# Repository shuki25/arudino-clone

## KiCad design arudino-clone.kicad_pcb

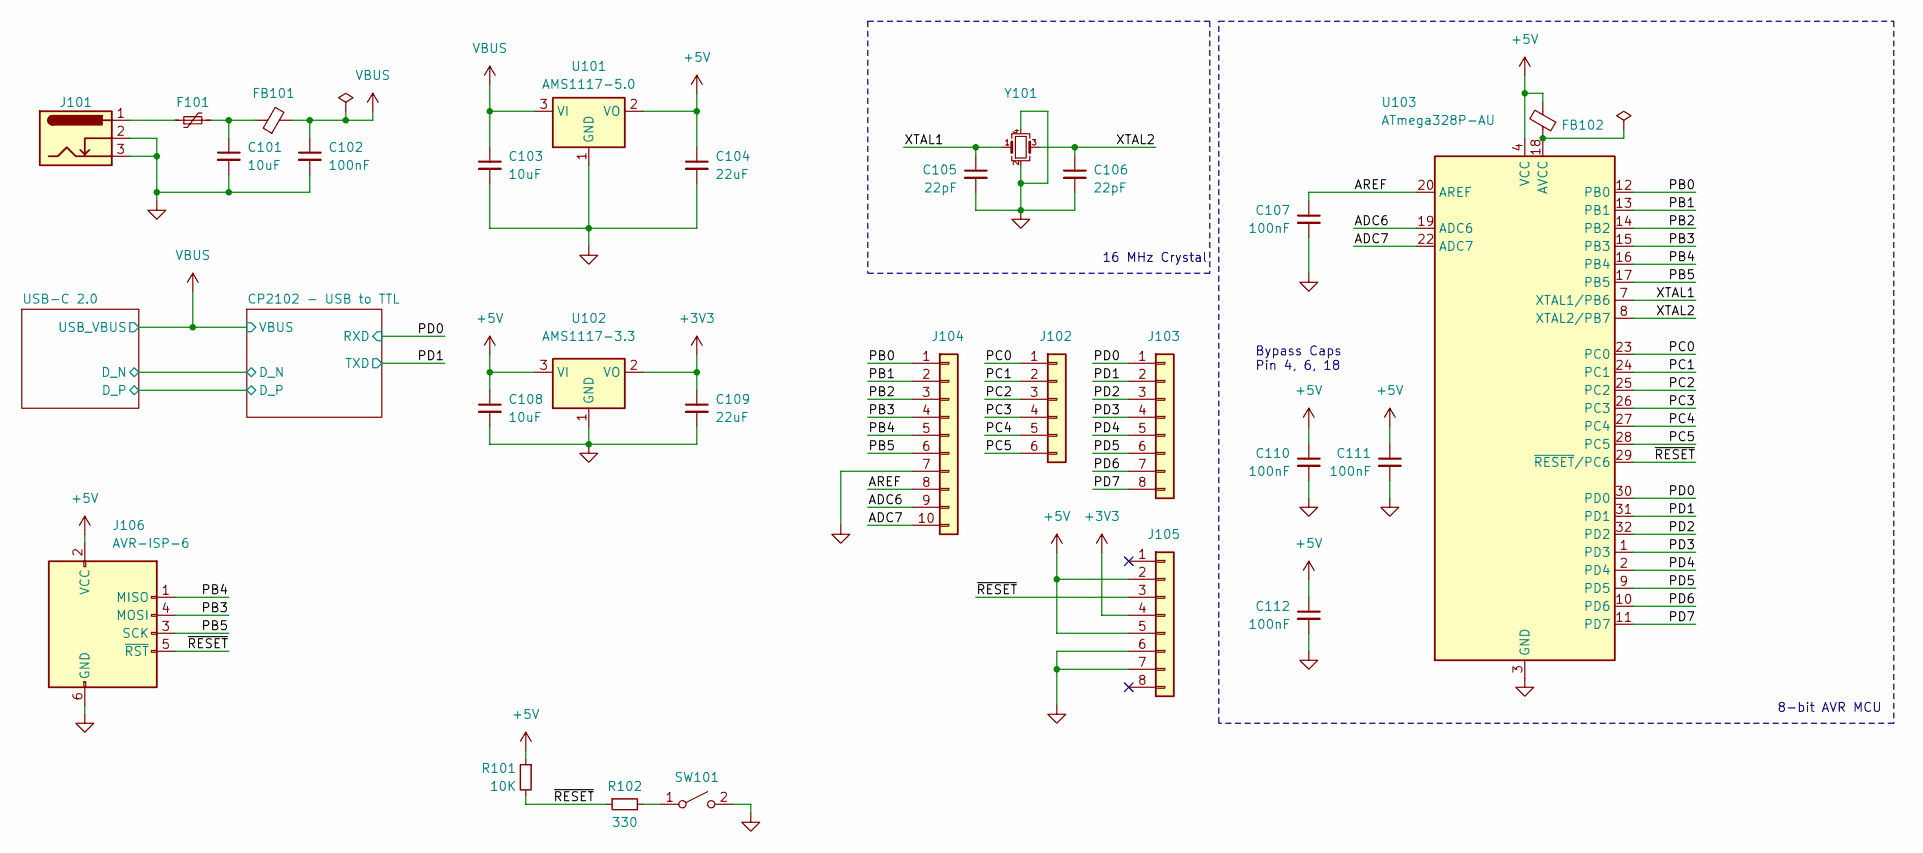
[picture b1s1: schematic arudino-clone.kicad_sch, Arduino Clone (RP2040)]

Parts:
C101, C103, C108: 10uF; C_0805_2012Metric; LCSC C15850
C102, C107, C110, C111, C112: 100nF; C_0603_1608Metric; LCSC C14663
C104, C109: 22uF; C_0805_2012Metric; LCSC C45783
C105, C106: 22pF; C_0603_1608Metric; LCSC C1653
F101: Polyfuse_Small; Fuse_1206_3216Metric; LCSC C883135
FB101, FB102: FerriteBead_Small; R_0805_2012Metric; LCSC C74487
J101: Barrel_Jack; BarrelJack_Wuerth_6941xx301002
J102: Conn_01x06; PinSocket_1x06_P2.54mm_Vertical
J103, J105: Conn_01x08; PinSocket_1x08_P2.54mm_Vertical
J104: Conn_01x10; PinSocket_1x10_P2.54mm_Vertical
J106: AVR-ISP-6; TC2030-IDC-NL
R101: 10K; R_0603_1608Metric; LCSC C25804
R102: 330; R_0603_1608Metric; LCSC C25804
SW101: SW_SPST; XKB-Connectivity-TS-1187A-B-A-B; LCSC C318884
U101: AMS1117-5.0; SOT-223-3_TabPin2; LCSC C6187
U102: AMS1117-3.3; SOT-223-3_TabPin2; LCSC C6186
U103: ATmega328P-AU; TQFP-32_7x7mm_P0.8mm; LCSC C14877
Y101: Crystal_GND24_Small; Crystal_SMD_3225-4Pin_3.2x2.5mm; LCSC C13738

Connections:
+3V3: C109.1, J105.4, U102.2 (VO)
+5V: C104.1, C108.1, C110.1, C111.1, C112.1, FB102.2, J105.2, J105.5, J106.2 (VCC), R101.1, U101.2 (VO), U102.3 (VI), U103.4 (VCC), U103.6 (VCC)
/ADC6: J104.9, U103.19 (ADC6)
/ADC7: J104.10, U103.22 (ADC7)
/AREF: C107.1, J104.8, U103.20 (AREF)
/PB0: J104.1, U103.12 (PB0)
/PB1: J104.2, U103.13 (PB1)
/PB2: J104.3, U103.14 (PB2)
/PB3: J104.4, J106.4 (MOSI), U103.15 (PB3)
/PB4: J104.5, J106.1 (MISO), U103.16 (PB4)
/PB5: J104.6, J106.3 (SCK), U103.17 (PB5)
/PC0: J102.1, U103.23 (PC0)
/PC1: J102.2, U103.24 (PC1)
/PC2: J102.3, U103.25 (PC2)
/PC3: J102.4, U103.26 (PC3)
/PC4: J102.5, U103.27 (PC4)
/PC5: J102.6, U103.28 (PC5)
/PD0: J103.1, U103.30 (PD0); also elsewhere on the board
/PD1: J103.2, U103.31 (PD1); also elsewhere on the board
/PD2: J103.3, U103.32 (PD2)
/PD3: J103.4, U103.1 (PD3)
/PD4: J103.5, U103.2 (PD4)
/PD5: J103.6, U103.9 (PD5)
/PD6: J103.7, U103.10 (PD6)
/PD7: J103.8, U103.11 (PD7)
/XTAL1: C105.1, U103.7 (XTAL1/PB6), Y101.1
/XTAL2: C106.1, U103.8 (XTAL2/PB7), Y101.3
/~RESET: J105.3, J106.5 (~RST), R101.2, R102.1, U103.29 (~RESET/PC6)
GND: C101.2, C102.2, C103.2, C104.2, C105.2, C106.2, C107.2, C108.2, C109.2, C110.2, C111.2, C112.2, J101.2, J101.3, J104.7, J105.6, J105.7, J106.6 (GND), SW101.2 (B), U101.1 (GND), U102.1 (GND), U103.3 (GND), U103.5 (GND), U103.21 (GND), Y101.2, Y101.4; also elsewhere on the board
unnamed: F101.1, J101.1
unnamed: R102.2, SW101.1 (A)
unnamed: FB102.1, U103.18 (AVCC)
VBUS: C102.1, C103.1, FB101.2, U101.3 (VI); also elsewhere on the board

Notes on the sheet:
Bypass Caps Pin 4, 6, 18
16 MHz Crystal
8-bit AVR MCU

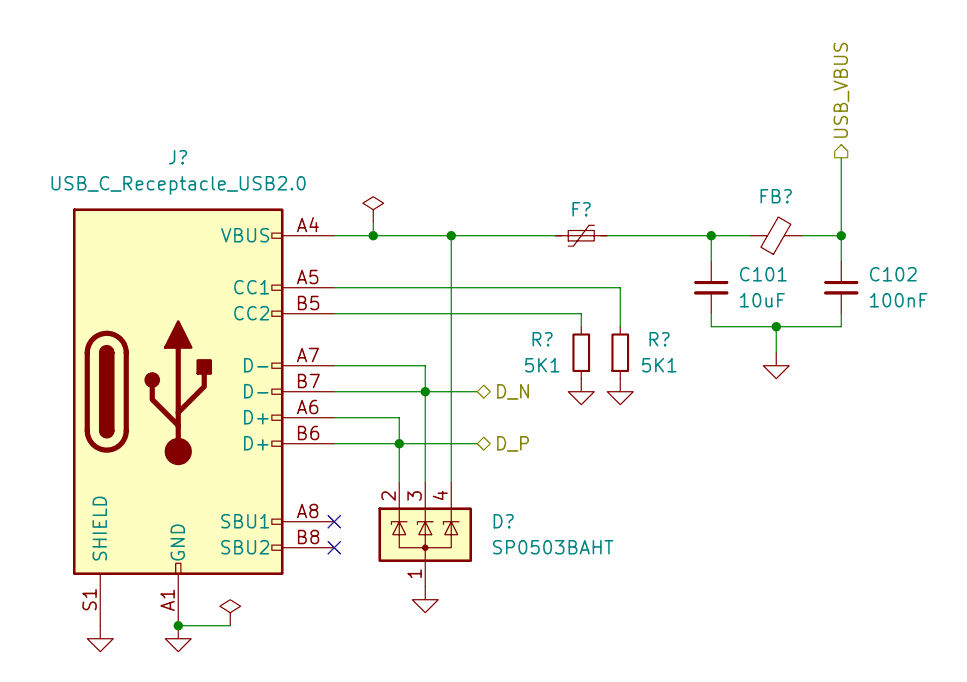
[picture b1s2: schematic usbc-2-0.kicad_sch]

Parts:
C101: 10uF; C_0805_2012Metric; LCSC C15850
C102: 100nF; C_0603_1608Metric; LCSC C14663
D201: SP0503BAHT; SOT-143; LCSC C7074
F201: Polyfuse_Small; Fuse_0603_1608Metric; LCSC C2757930
FB201: FerriteBead_Small; R_0805_2012Metric; LCSC C74487
J201: USB_C_Receptacle_USB2.0; USB_C_Receptable_918-418K2023S40001; LCSC C2982555
R201, R202: 5K1; C_0603_1608Metric; LCSC C23186

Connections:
/CP2102 - USB to TTL/D_N: D201.3 (K), J201.A7 (D-), J201.B7 (D-); also elsewhere on the board
/CP2102 - USB to TTL/D_P: D201.2 (K), J201.A6 (D+), J201.B6 (D+); also elsewhere on the board
GND: C101.2, C102.2, D201.1 (A), J201.A1 (GND), J201.A12 (GND), J201.B1 (GND), J201.B12 (GND), J201.S1 (SHIELD), R201.1, R202.1; also elsewhere on the board
unnamed: D201.4 (K), F201.1, J201.A4 (VBUS), J201.A9 (VBUS), J201.B4 (VBUS), J201.B9 (VBUS)
unnamed: J201.A5 (CC1), R202.2
unnamed: J201.B5 (CC2), R201.2
VBUS: C102.1, FB201.2; also elsewhere on the board

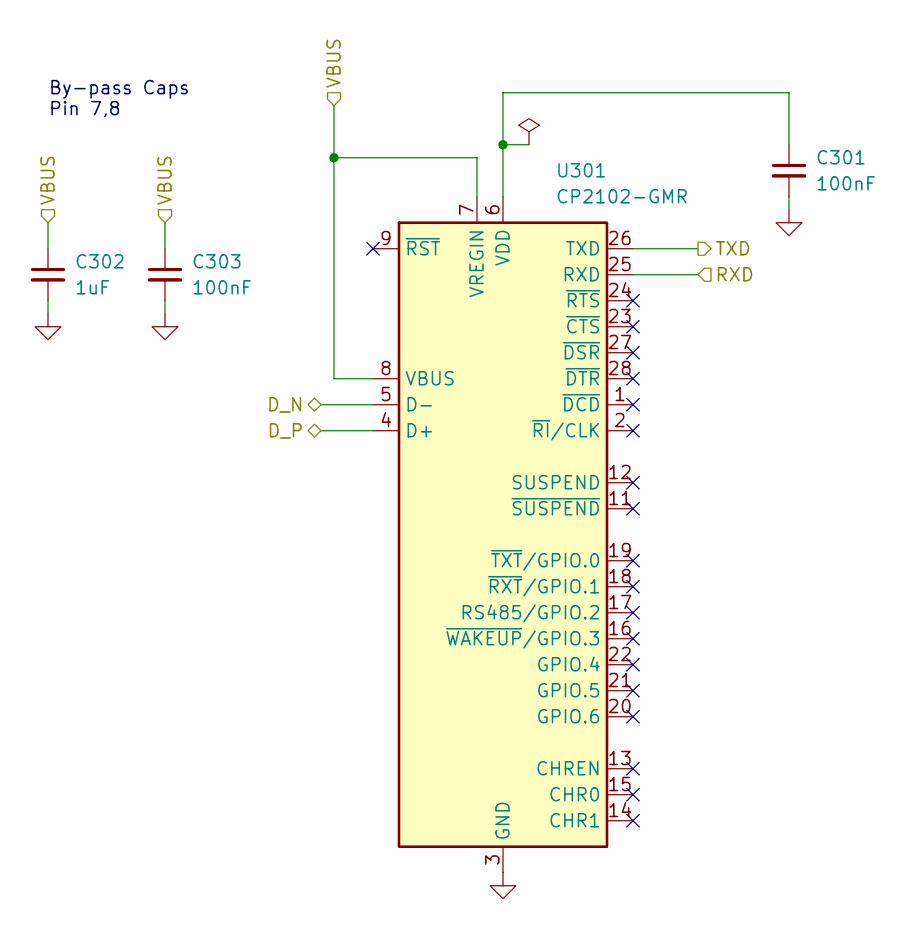
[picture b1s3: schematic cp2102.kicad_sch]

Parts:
C301, C303: 100nF; C_0603_1608Metric; LCSC C14663
C302: 1uF; C_0603_1608Metric; LCSC C14663
U301: CP2102-GMR; QFN-28-1EP_5x5mm_P0.5mm_EP3.35x3.35mm; LCSC C6568

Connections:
/CP2102 - USB to TTL/D_N: U301.5 (D-); also elsewhere on the board
/CP2102 - USB to TTL/D_P: U301.4 (D+); also elsewhere on the board
/PD0: U301.25 (RXD); also elsewhere on the board
/PD1: U301.26 (TXD); also elsewhere on the board
GND: C301.2, C302.2, C303.2, U301.3 (GND), U301.29 (GND); also elsewhere on the board
unnamed: C301.1, U301.6 (VDD)
VBUS: C302.1, C303.1, U301.7 (VREGIN), U301.8 (VBUS); also elsewhere on the board

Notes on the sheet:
By-pass Caps Pin 7,8

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
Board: 2 copper layers, 40 parts (0 on the bottom side), 41 nets, no tracks yet.

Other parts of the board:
C201: 10uF; C_0805_2012Metric
C202: 100nF; C_0603_1608Metric

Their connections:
GND: C201.2, C202.2; also elsewhere on the board
VBUS: C202.1; also elsewhere on the board

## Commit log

2023-02-01 add initial components and initial PCB layout
2023-02-06 updated caps and power regulator
2023-02-28 update schematic
